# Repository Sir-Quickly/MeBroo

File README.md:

# #MeBroo
Erweiterungsboard für den RaspberryPi zur Brau-Automatisierung

Known Issues: - LEDs falsch angeschlossen, Handpatch notwendig

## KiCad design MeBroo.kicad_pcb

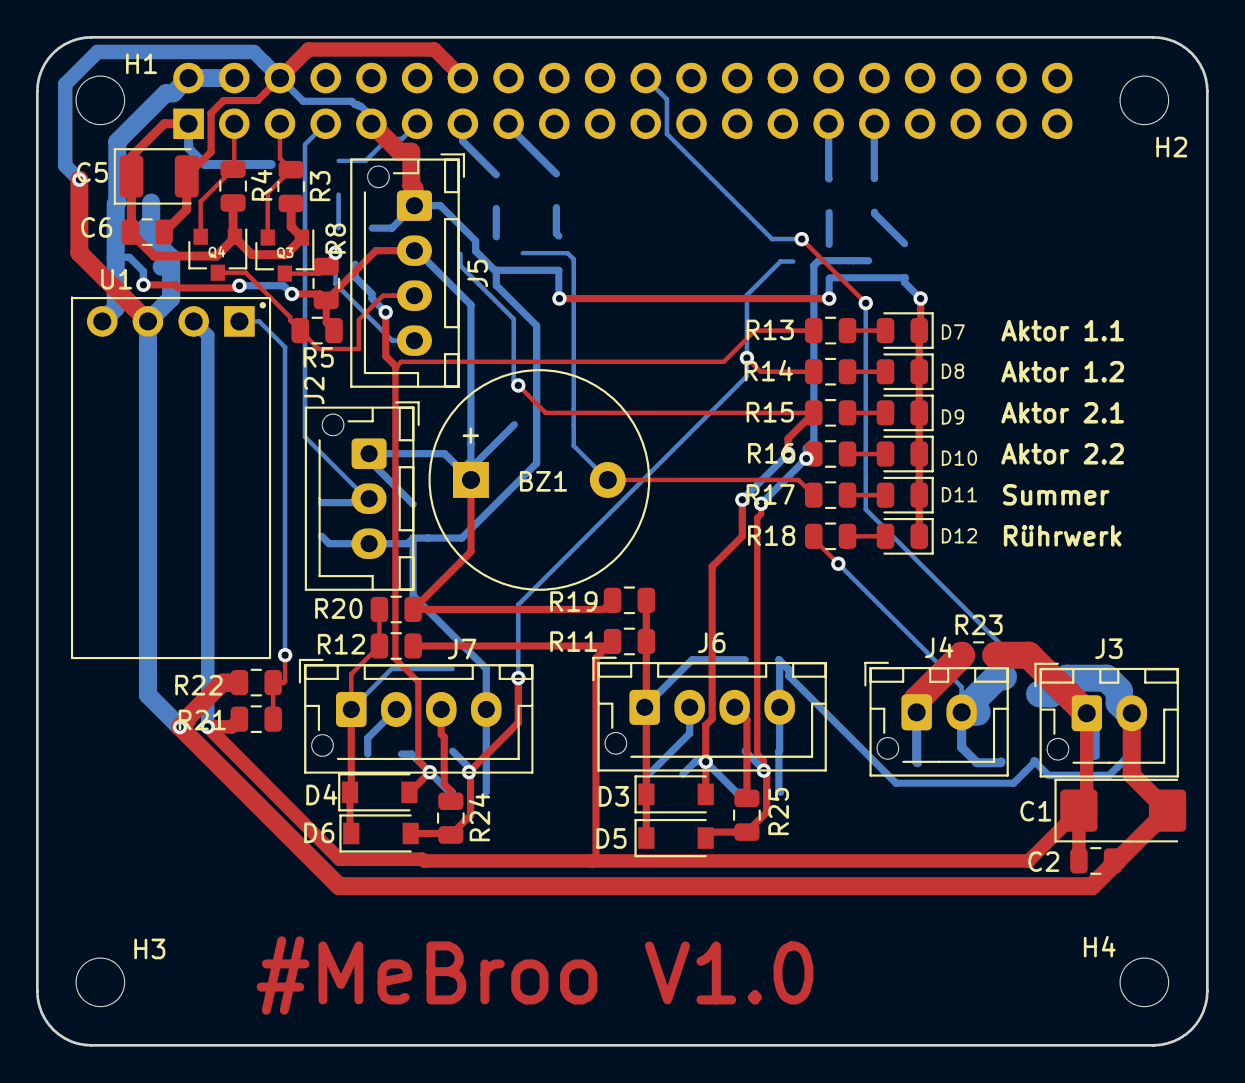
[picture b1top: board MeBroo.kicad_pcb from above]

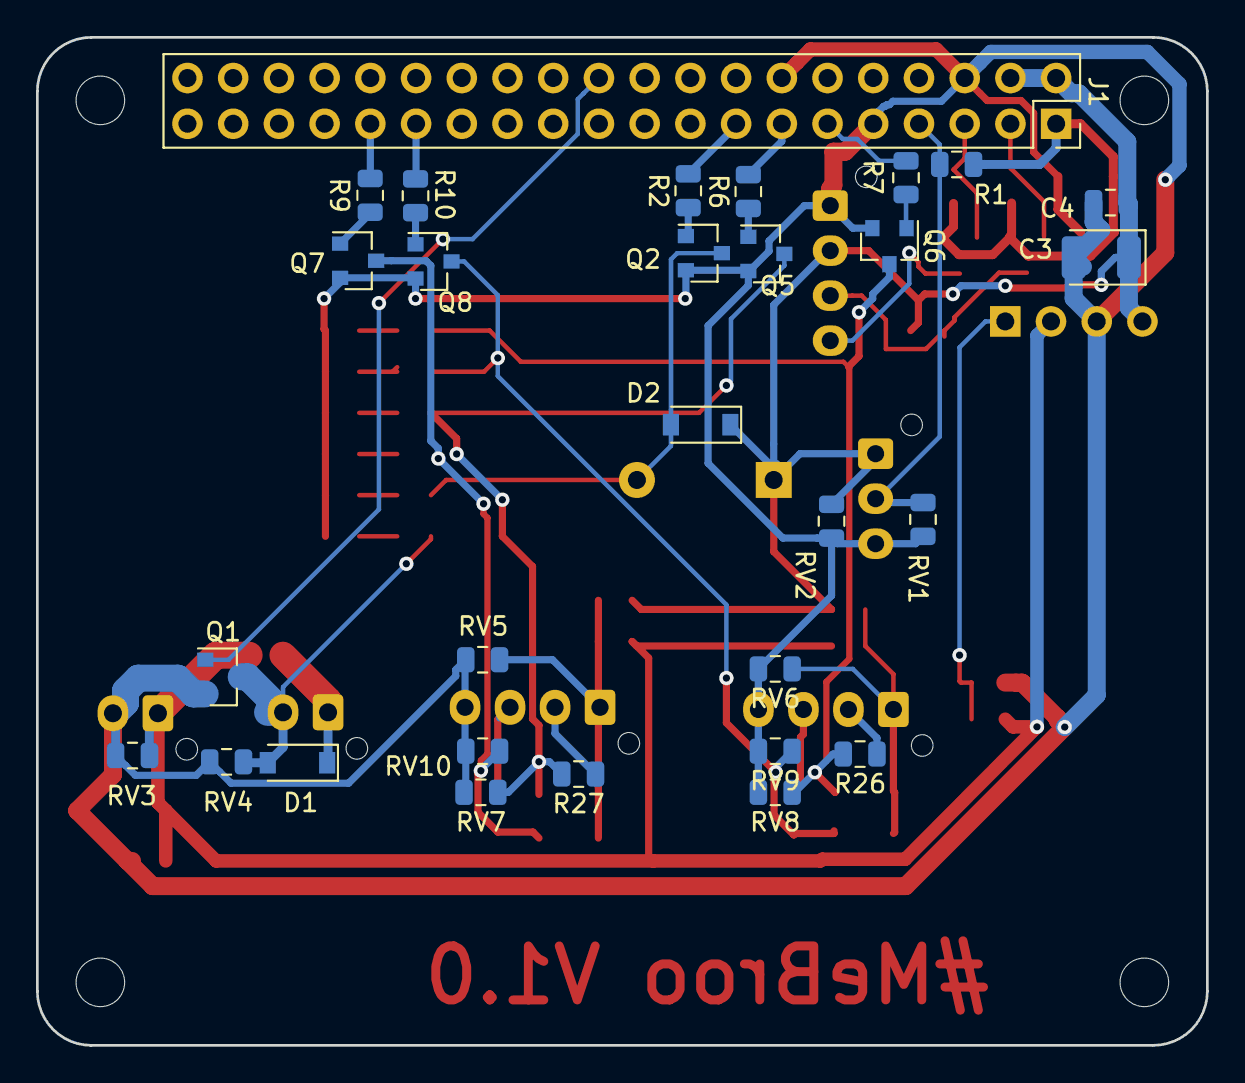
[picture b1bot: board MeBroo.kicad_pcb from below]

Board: 2 copper layers, 65.0 x 56.0 mm, 76 parts (29 on the bottom side), 40 nets.

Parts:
BZ1: Buzzer; Buzzer_12x9.5RM7.6
C1: CP; CP_EIA-6032-28_Kemet-C
C2, C4, C6: C; C_0805_2012Metric
C3, C5: CP; CP_EIA-3528-21_Kemet-B
D1, D2, D3, D4, D5, D6: 1N4148W; D_SOD-123
D7, D8, D9, D10, D11, D12: green; LED_0805_2012Metric
H1, H2, H3, H4: MountingHole; MountingHole_2.7mm_M2.5_ISO7380
J1: Conn_02x20_Odd_Even; PinSocket_2x20_P2.54mm_Vertical
J2: Conn_01x03; JST_XH_B03B-XH-AM_1x03_P2.50mm_Vertical
J3, J4: Conn_01x02; JST_XH_B02B-XH-AM_1x02_P2.50mm_Vertical
J5, J6, J7: Conn_01x04; JST_XH_B04B-XH-AM_1x04_P2.50mm_Vertical
Q1: IRLML6244; SOT-23
Q2, Q5, Q6, Q7, Q8: BC848; SOT-23
Q3, Q4: 2N7002; SOT-23
R1: 4k7; R_0805_2012Metric
R2, R6, R7, R9, R10, R11, R13, R14, R15, R16, R17, R18, R19, R24, R25, R26, R27: R; R_0805_2012Metric
R3, R4, R5, R8: 10k; R_0805_2012Metric
R12, R20, R21, R22, R23: 0R; R_0805_2012Metric
RV1, RV2, RV3, RV4, RV5, RV6, RV7, RV8, RV9, RV10: Varistor; Varistor_0805_2012Metric
U1: TE818; TE818_SwitchingRegulator_Module

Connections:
+3V3: C5.1, C6.1, J1.1, J1.17, Q3.1, Q4.1, R1.2, R3.2, R4.2
+5V: BZ1.1, C3.1, C4.1, D2.1, J1.2, J1.4, J2.1, J5.2, R5.2, R8.2, R19.1, R20.1, RV2.1, U1.4
+12V: C1.1, C2.1, J3.1, R11.1, R12.1, R21.2, R23.2, RV3.1, U1.2
/AKT_1_1: D4.2, Q6.3, R13.1, R26.2, RV8.1
/AKT_1_2: D6.2, Q8.3, R14.1, R24.2, RV9.1
/AKT_2_1: D3.2, Q5.3, R15.1, R27.2, RV7.1
/AKT_2_2: D5.2, Q7.3, R16.1, R25.2, RV10.1
/BUZZER: BZ1.2, D2.2, Q2.3, R17.1
/GPIO_4: J1.7, J2.2, R1.1, RV1.1
/GPIO_5: J1.29, R10.2
/GPIO_6: J1.31, R9.2
/GPIO_17: J1.11, R7.2
/GPIO_22: J1.15, R2.2
/GPIO_25: J1.22, Q1.1
/GPIO_27: J1.13, R6.2
/SCL: J1.5, Q3.2, R3.1
/SCL_5V: J5.4, Q3.3, R8.1
/SDA: J1.3, Q4.2, R4.1
/SDA_5V: J5.3, Q4.3, R5.1
/STIRRER: D1.2, J4.2, Q1.3, R18.1, RV4.1
GND: C1.2, C2.2, C3.2, C4.2, C5.2, C6.2, D7.1, D8.1, D9.1, D10.1, D11.1, D12.1, J1.6, J1.9, J1.14, J1.20, J1.25, J1.30, J1.34, J1.39, J2.3, J3.2, J5.1, J6.4, J7.4, Q1.2, Q2.2, Q5.2, Q6.2, Q7.2, Q8.2, R22.2, RV1.2, RV2.2, RV3.2, RV4.2, RV5.2, RV6.2, RV7.2, RV8.2, RV9.2, RV10.2, U1.3
unnamed: D1.1, J4.1, R23.1
unnamed: D3.1, D5.1, J6.1, R11.2, R19.2, RV5.1
unnamed: D4.1, D6.1, J7.1, R12.2, R20.2, RV6.1
unnamed: D7.2, R13.2
unnamed: D8.2, R14.2
unnamed: D9.2, R15.2
unnamed: D10.2, R16.2
unnamed: D11.2, R17.2
unnamed: D12.2, R18.2
unnamed: J6.2, R27.1
unnamed: J6.3, R25.1
unnamed: J7.2, R26.1
unnamed: J7.3, R24.1
unnamed: Q2.1, R2.1
unnamed: Q5.1, R6.1
unnamed: Q6.1, R7.1
unnamed: Q7.1, R9.1
unnamed: Q8.1, R10.1
unnamed: R21.1, R22.1, U1.1

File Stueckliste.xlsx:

ID | Bezeichner | GehÃ¤use | StÃ¼ckzahl | Bezeichnung | Anbieter und Referenz
1 | D3,D2,D4,D5,D6,D1 | D_SOD-123 | 6 | 1N4148W | RND 1N4148W
2 | RV8,RV6,RV9,RV7,RV1,RV2,RV3,RV5,RV4,RV10 | Varistor_0805_2012Metric | 10 | Varistor | VC 0805-14
3 | R27,R25,R26,R24 | R_0805_2012Metric | 4 | 10R | SMD-0805 10,0
4 | R23,R22,R21,R20,R12,R11,R19 | R_0805_2012Metric | 7 | 0R | SMD-0805 0,00
5 | U1 | TE818_SwitchingRegulator_Module | 1 | TE818 | Ebay
6 | J5,J6,J7 | JST_XH_B04B-XH-AM_1x04_P2.50mm_Vertical | 3 | Conn_01x04 | JST XH4P ST
7 | Q2,Q7,Q8,Q6,Q5 | SOT-23 | 5 | BC848 | BC 848C INF
8 | C3,C5 | CP_EIA-3528-21_Kemet-B | 2 | 4u7/6V3 | TPS 3225 100/6,3
9 | R10,R2,R9,R7,R6 | R_0805_2012Metric | 5 | 2k2 | SMD-0805 2,20K
10 | R3,R5,R4,R8 | R_0805_2012Metric | 4 | 10k | SMD-0805 10,0K
11 | R1 | R_0805_2012Metric | 1 | 4k7 | SMD-0805 4,70K
12 | Q3,Q4 | SOT-23 | 2 | 2N7002 | 2N 7002KT1G ONS
13 | J1 | PinSocket_2x20_P2.54mm_Vertical | 1 | Conn_02x20_Odd_Even
14 | C2,C4,C6 | C_0805_2012Metric | 3 | 100n | KEM X7R0805 100N
15 | C1 | CP_EIA-6032-28_Kemet-C | 1 | 100u/16V | TPS 6032 100/16
16 | J3,J4 | JST_XH_B02B-XH-AM_1x02_P2.50mm_Vertical | 2 | Conn_01x02 | JST XH2P ST
17 | D7,D8,D9,D10 | LED_0805_2012Metric | 4 | green | OSO LGR971
18 | D11 | LED_0805_2012Metric | 1 | red | OSO LSR976
19 | D12 | LED_0805_2012Metric | 1 | orange | OSO LOR976
20 | R17,R16,R15,R14,R13 | R_0805_2012Metric | 5 | 1k2 | SMD-0805 4,70K
21 | R18 | R_0805_2012Metric | 1 | 4K7 | SMD-0805 4,70K
22 | BZ1 | Buzzer_12x9.5RM7.6 | 1 | Buzzer | VIS 3590
23 | Q1 | SOT-23 | 1 | IRLML6244 | IRLML 6244
24 | H4,H3,H2,H1 | MountingHole_2.7mm_M2.5_ISO7380 | 4 | MountingHole
25 | J2 | JST_XH_B03B-XH-AM_1x03_P2.50mm_Vertical | 1 | Conn_01x03 | JST XH3P ST

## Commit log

2020-06-02 initial commit of project to GitHub
2020-06-04 fixed libraryy issue
2020-06-04 some editorial housekeeping
2020-06-07 required Hanpatch and partlist added to repo
